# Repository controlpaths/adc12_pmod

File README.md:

# PMOD ADC12

PMOD with an ADC and an analog circuit to read signals up to +-12V. The PMOD uses the ADC [ADC122S021](https://www.ti.com/lit/ds/symlink/adc122s021.pdf?ts=1709486131740&ref_url=https%253A%252F%252Fwww.google.com%252F) from TI.

To read negative signals, the analog circuit inserts an offset voltage before the signal in connected to the ADC. This offset is always VCC/2. 

In addition, a first-order low pass filter is added in both input channels.

## PMOD interface

This PMOD uses an SPI interface to read the ADC. The pinout of the board is shown in the next image.

The SPi connection is different than the PMOD SPI standard.

## Images

## Get Yours

The PMOD ADC12 is open-source, so you can use the output files to manufacture your own in [JLCPCB](https://jlcpcb.com/?from=controlpath). You just need to compress the `output_files` directory, and upload it to [JLCPCB](https://jlcpcb.com/?from=controlpath). 

Remember to change the Surface Finish to **LeadFree HASL** to make your board ROHS compliant.

Then you have to add the PCB Assembly service and upload the [centroid](./kicad/output_files/pmod_adc12-all-pos.csv) file, and the [BOM](./kicad/output_files/bom.csv). 

In a few days, you will receive your board at home. If you want just one PMOD ADC12, contact me.

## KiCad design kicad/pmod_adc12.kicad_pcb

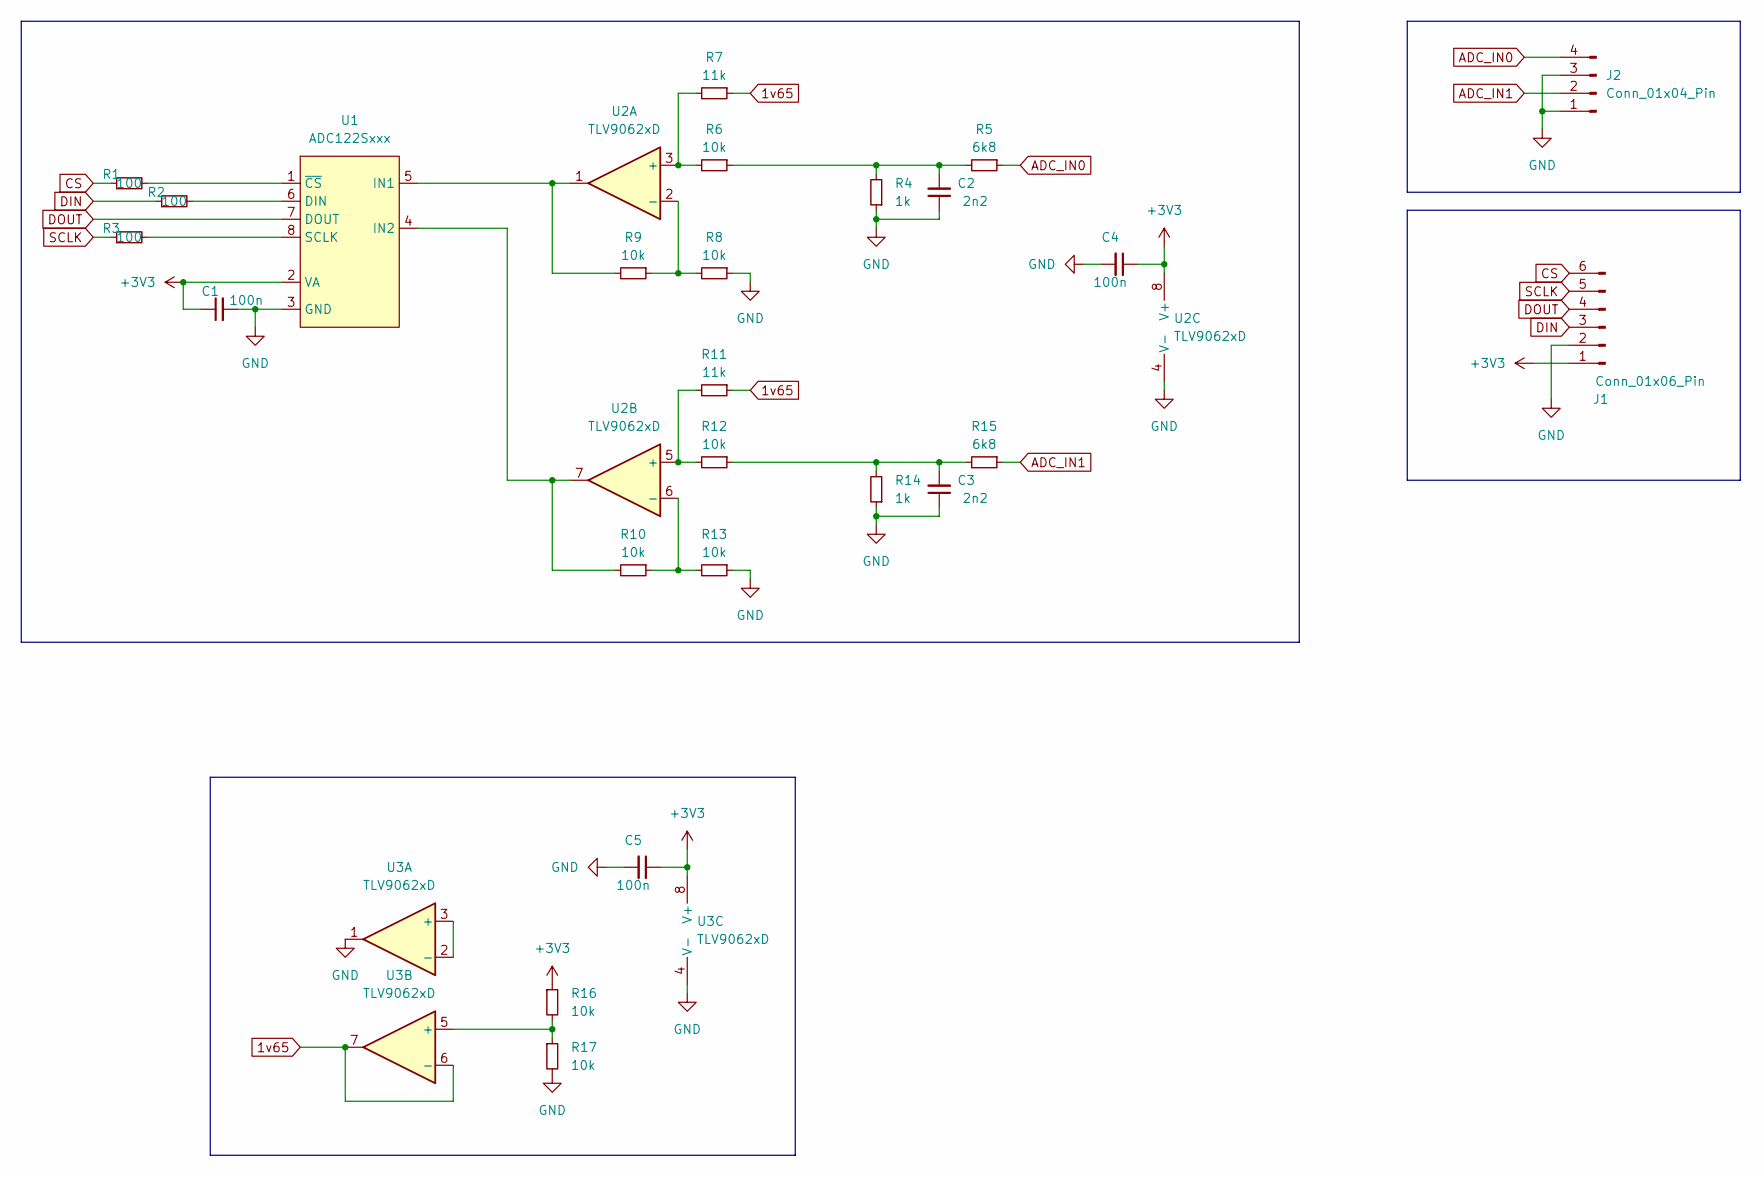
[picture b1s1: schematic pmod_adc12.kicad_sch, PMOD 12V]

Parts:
C1, C4, C5: 100n; C_0603_1608Metric
C2, C3: 2n2; C_0603_1608Metric
J1: Conn_01x06_Pin; PinHeader_1x06_P2.54mm_Horizontal
J2: Conn_01x04_Pin; PinHeader_1x04_P2.54mm_Horizontal
R1, R2, R3: 100; R_0603_1608Metric
R4, R14: 1k; R_0603_1608Metric
R5, R15: 6k8; R_0603_1608Metric
R6, R8, R9, R10, R12, R13, R16, R17: 10k; R_0603_1608Metric
R7, R11: 11k; R_0603_1608Metric
U1: ADC122Sxxx; VSSOP-8_3.0x3.0mm_P0.65mm; JLCPCB Part # C528639
U2, U3: TLV9062xD; SOIC-8_3.9x4.9mm_P1.27mm; JLCPCB Part # C398355

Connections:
1v65: R7.1, R11.1, U3.6 (-), U3.7
+3V3: C1.1, C4.1, C5.1, J1.1, R16.1, U1.2 (VA), U2.8 (V+), U3.8 (V+)
ADC_IN0: J2.4, R5.1
ADC_IN1: J2.2, R15.1
CS: J1.6, R1.1
DIN: J1.3, R2.1
DOUT: J1.4, U1.7 (DOUT)
GND: C1.2, C2.1, C3.1, C4.2, C5.2, J1.2, J2.1, J2.3, R4.1, R8.1, R13.1, R14.1, R17.2, U1.3 (GND), U2.4 (V-), U3.1, U3.4 (V-)
unnamed: C2.2, R4.2, R5.2, R6.1
unnamed: C3.2, R12.1, R14.2, R15.2
unnamed: R2.2, U1.6 (DIN)
unnamed: R9.2, U1.5 (IN1), U2.1
unnamed: R10.2, U1.4 (IN2), U2.7
unnamed: R3.2, U1.8 (SCLK)
unnamed: R1.2, U1.1 (~CS)
unnamed: R6.2, R7.2, U2.3 (+)
unnamed: R8.2, R9.1, U2.2 (-)
unnamed: R11.2, R12.2, U2.5 (+)
unnamed: R10.1, R13.2, U2.6 (-)
unnamed: U3.2 (-), U3.3 (+)
unnamed: R16.2, R17.1, U3.5 (+)
SCLK: J1.5, R3.1

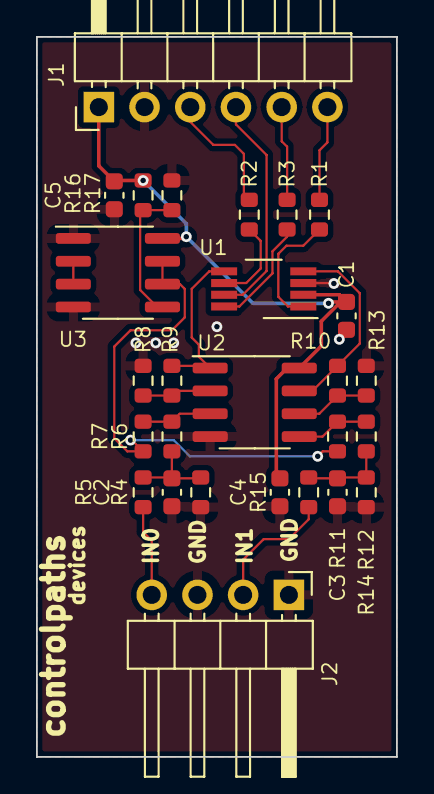
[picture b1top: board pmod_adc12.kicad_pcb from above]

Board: 2 copper layers, 20.0 x 40.0 mm, 27 parts (0 on the bottom side), 22 nets.

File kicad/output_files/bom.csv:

#,Reference,Qty,Value,Footprint,DNP,JLCPCB Part #
1,"C1, C4, C5",3,100n,Capacitor_SMD:C_0603_1608Metric,,
2,"C2, C3",2,2n2,Capacitor_SMD:C_0603_1608Metric,,
3,J1,1,Conn_01x06_Pin,Connector_PinHeader_2.54mm:PinHeader_1x06_P2.54mm_Horizontal,,C2894948
4,J2,1,Conn_01x04_Pin,Connector_PinHeader_2.54mm:PinHeader_1x04_P2.54mm_Horizontal,,C7501292
5,"R1, R2, R3",3,100,Resistor_SMD:R_0603_1608Metric,,
6,"R4, R14",2,1k,Resistor_SMD:R_0603_1608Metric,,
7,"R5, R15",2,6k8,Resistor_SMD:R_0603_1608Metric,,
8,"R6, R8, R9, R10, R12, R13, R16, R17",8,10k,Resistor_SMD:R_0603_1608Metric,,
9,"R7, R11",2,11k,Resistor_SMD:R_0603_1608Metric,,
10,U1,1,ADC122Sxxx,Package_SO:VSSOP-8_3.0x3.0mm_P0.65mm,,C528639
11,"U2, U3",2,TLV9062xD,Package_SO:SOIC-8_3.9x4.9mm_P1.27mm,,C398355

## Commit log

2024-03-03 added all files
